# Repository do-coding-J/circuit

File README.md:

# circuit

## 1. [L298n](L298n_copy) 회로 복사

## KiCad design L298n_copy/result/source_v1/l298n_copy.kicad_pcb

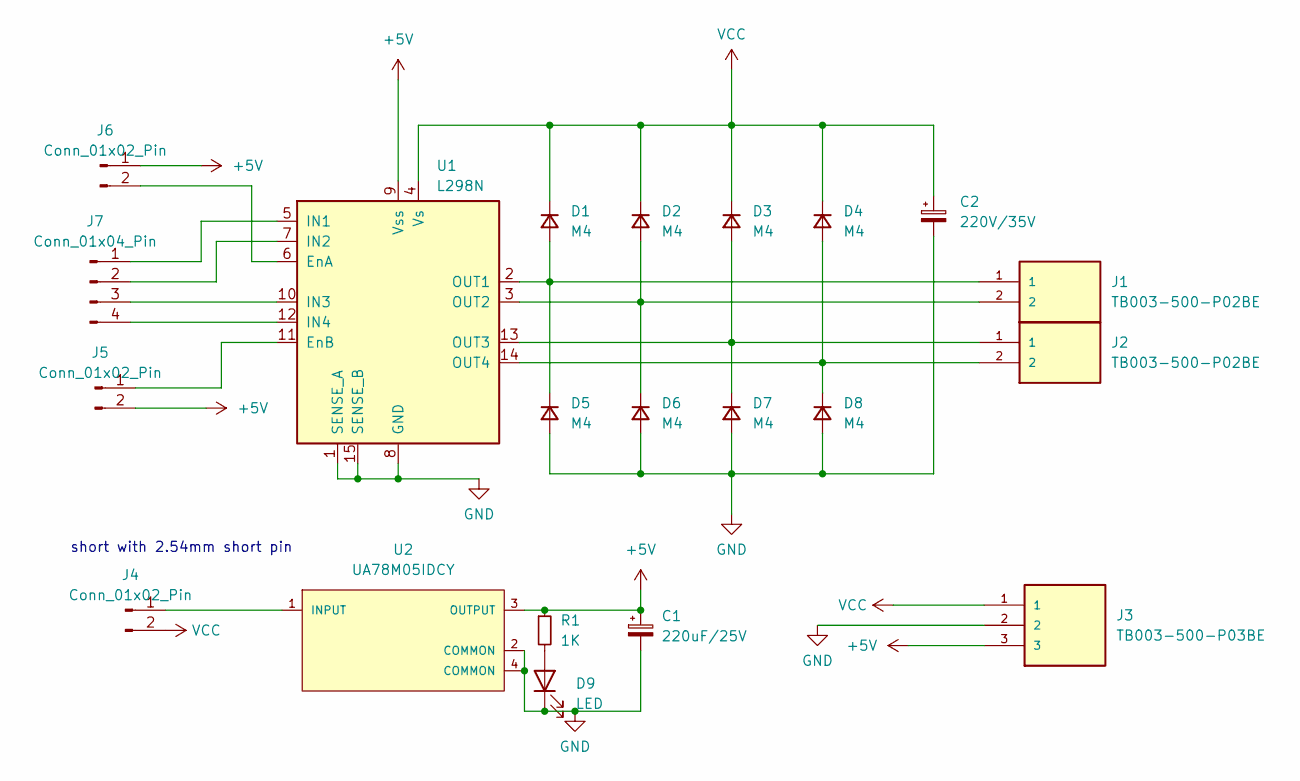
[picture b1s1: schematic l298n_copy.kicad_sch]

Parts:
C1: 220uF/25V; CP_Elec_10x10
C2: 220V/35V; CP_Elec_10x10
D1, D2, D3, D4, D5, D6, D7, D8: M4; D_SMA
D9: LED; R_0603_1608Metric
J1, J2: TB003-500-P02BE; CUI_TB003-500-P02BE
J3: TB003-500-P03BE; CUI_TB003-500-P03BE
J4, J5, J6: Conn_01x02_Pin; PinHeader_1x02_P2.54mm_Vertical
J7: Conn_01x04_Pin; PinHeader_1x04_P2.54mm_Vertical
R1: 1K; R_0603_1608Metric
U1: L298N; TO-220-15_P2.54x2.54mm_StaggerOdd_Lead4.58mm_Vertical
U2: UA78M05IDCY; Texas_Instruments-DCY0004A-0-0-0; dropout voltage 2V; output voltage 5V; mouser part number 595-UA78M05IDCY; digikey description IC REG LINEAR 5V 500MA SOT223-4

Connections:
+5V: C1.1, J3.3, J5.2, J6.1, R1.1, U1.9 (Vss), U2.3 (OUTPUT)
GND: C1.2, C2.2, D5.2 (A), D6.2 (A), D7.2 (A), D8.2 (A), D9.1 (K), J3.2, U1.1 (SENSE_A), U1.8 (GND), U1.15 (SENSE_B), U2.2 (COMMON), U2.4 (COMMON)
unnamed: D1.2 (A), D5.1 (K), J1.1, U1.2 (OUT1)
unnamed: D2.2 (A), D6.1 (K), J1.2, U1.3 (OUT2)
unnamed: D3.2 (A), D7.1 (K), J2.1, U1.13 (OUT3)
unnamed: D4.2 (A), D8.1 (K), J2.2, U1.14 (OUT4)
unnamed: D9.2 (A), R1.2
unnamed: J4.1, U2.1 (INPUT)
unnamed: J5.1, U1.11 (EnB)
unnamed: J6.2, U1.6 (EnA)
unnamed: J7.1, U1.5 (IN1)
unnamed: J7.2, U1.7 (IN2)
unnamed: J7.3, U1.10 (IN3)
unnamed: J7.4, U1.12 (IN4)
VCC: C2.1, D1.1 (K), D2.1 (K), D3.1 (K), D4.1 (K), J3.1, J4.2, U1.4 (Vs)

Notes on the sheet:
short with 2.54mm short pin

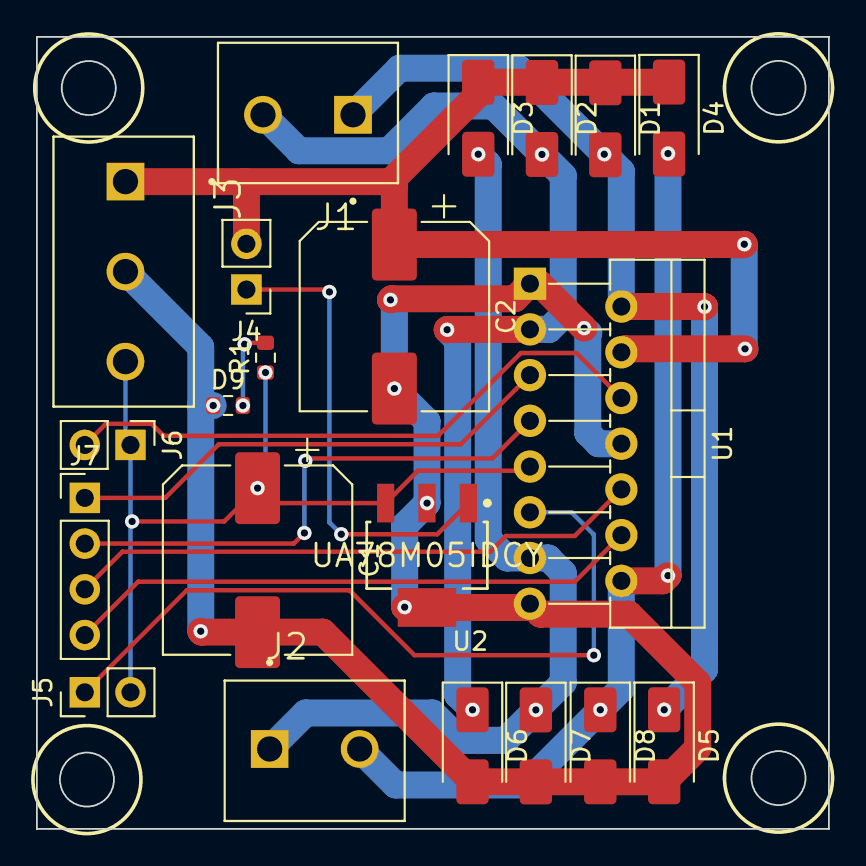
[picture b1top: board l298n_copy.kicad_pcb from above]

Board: 2 copper layers, 44.0 x 44.0 mm, 21 parts (0 on the bottom side), 15 nets.

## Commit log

2024-07-20 l298n copied
